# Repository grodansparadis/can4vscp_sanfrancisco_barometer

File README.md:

<h1>CAN4VSCP San Franscisco - barometer module</h1>

VSCP Barometer module.

<hr>

This project is part of the <a href="http://www.vscp.org">VSCP (Very Simple Control Protocol) project</a>. 

<hr>

This project is licensed under the 
<a href="http://creativecommons.org/licenses/by-nc-sa/3.0/">Creative Commons open source license Attribution-NonCommercial-ShareAlike 3.0 Unported</a>. 
Other license options are available by conacting <a href="malto:info@grodansparadis.com">Paradis of the Frog AB</a>

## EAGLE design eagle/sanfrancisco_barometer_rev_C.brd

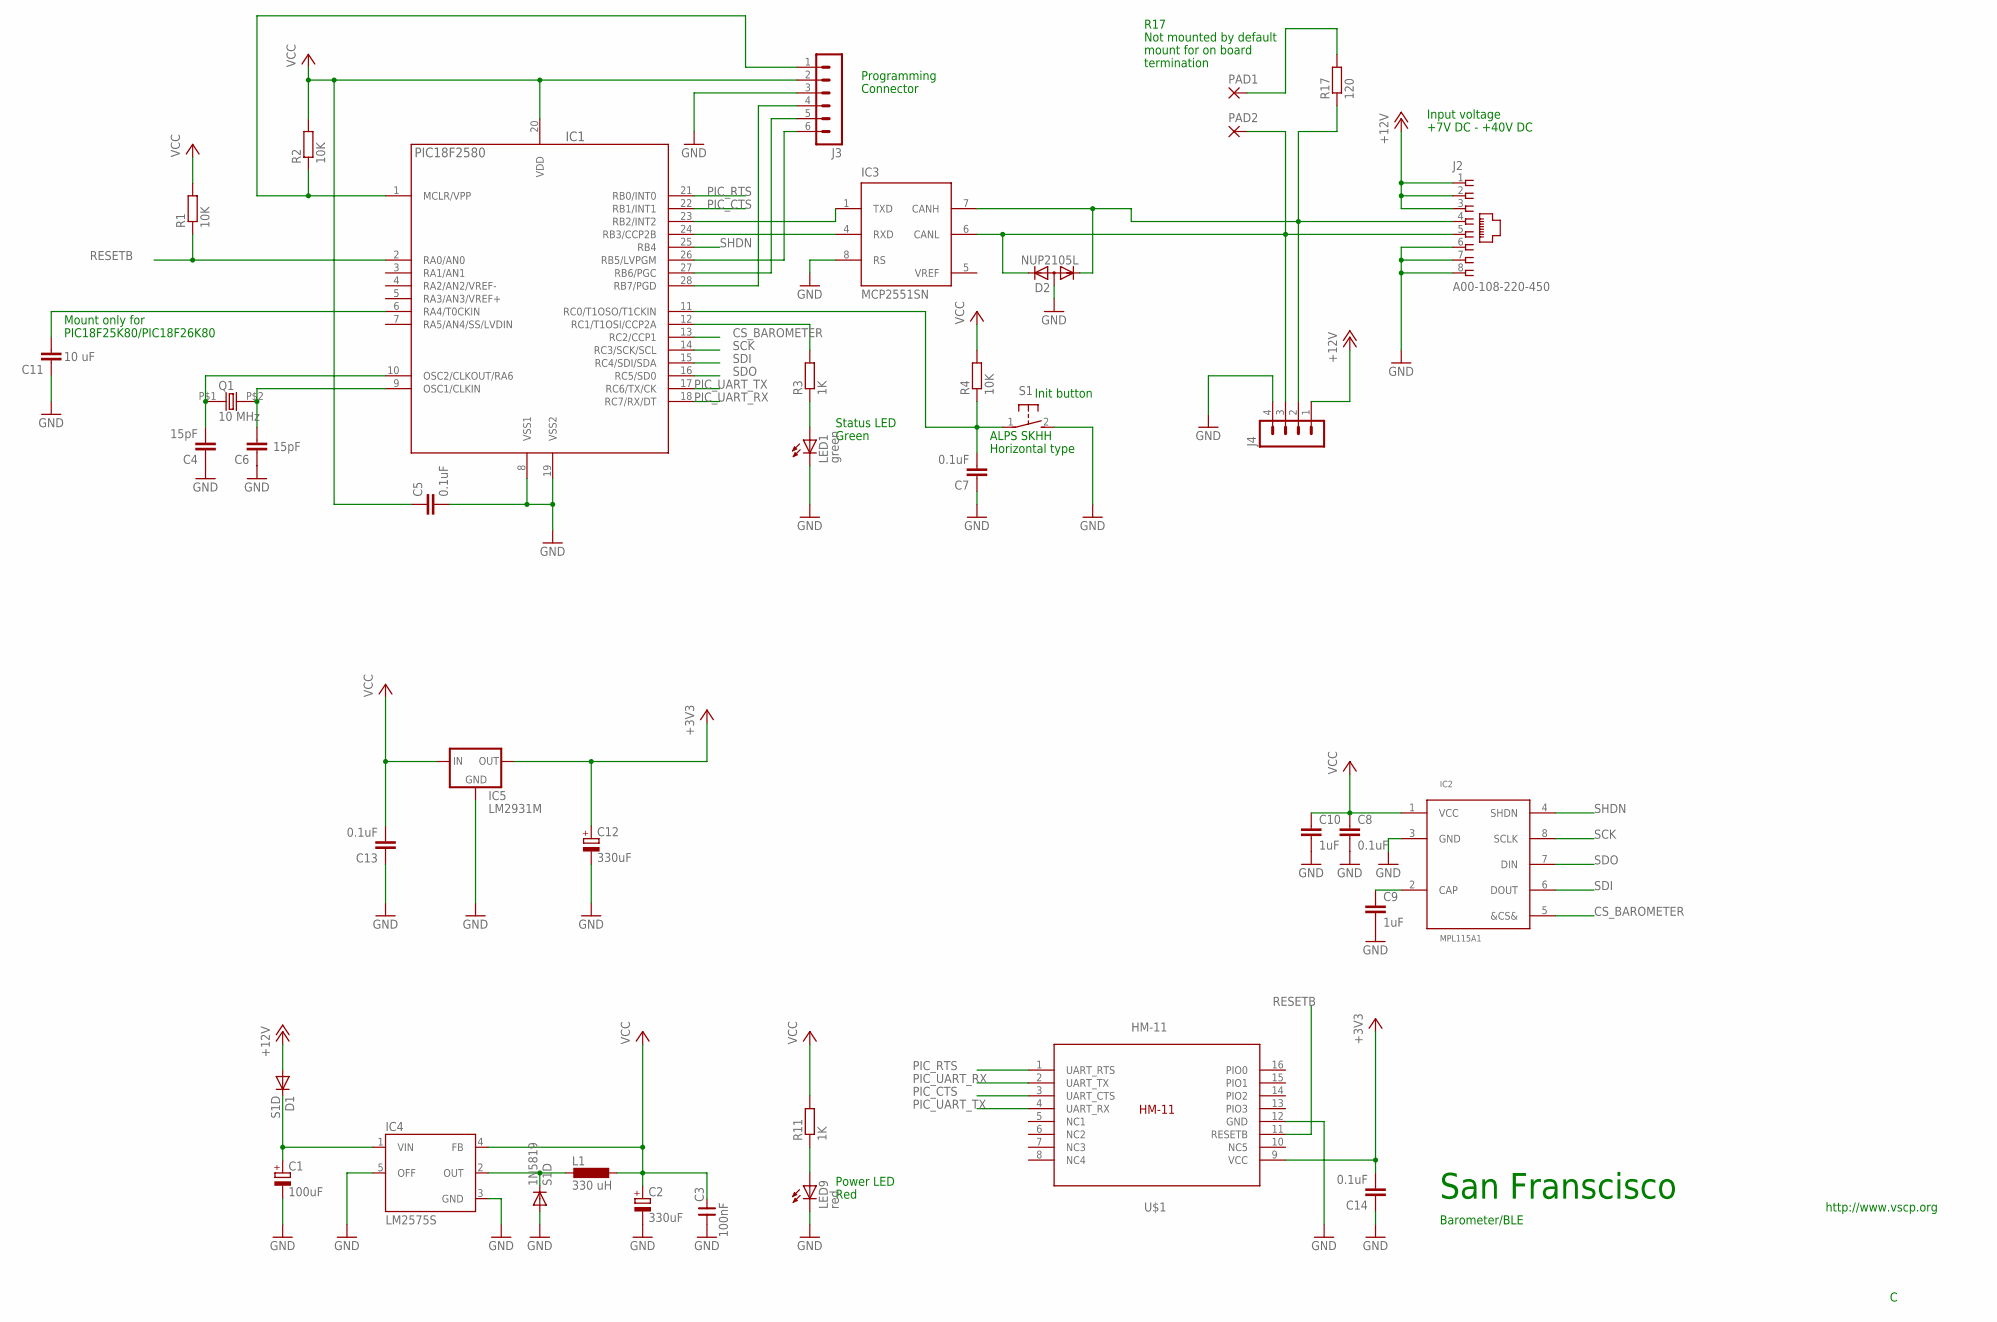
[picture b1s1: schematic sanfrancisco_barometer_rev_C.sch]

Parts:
1N5819: S1D; SOD123
C1: 100uF; PANASONIC_D
C2, C12: 330uF; PANASONIC_D
C3: 100nF; 0805
C4, C6: 15pF; C0805
C5, C7, C8, C13, C14: 0.1uF; C0805
C9, C10: 1uF; C0805
C11: 10 uF; C0805
D1: S1D; SOD123
D2: NUP2105L; SOT23
IC1: PIC18F2580; SO28
IC2: MPL115A1; LGA8
IC3: MCP2551SN; SO-08
IC4: LM2575S; TO263-5
IC5: LM2931M; SO08
J2: A00-108-220-450; RJ-45
J3: MA06-1
J4: MA04-1
L1: 330 uH; DO3316P
LED1: green; CHIP-LED0805
LED9: red; CHIP-LED0805
PAD1, PAD2: 1,6/0,8
Q1: 10 MHz; 9C
R1, R2, R4: 10K; R0805
R3, R11: 1K; R0805
R17: 120; R0805
S1: 31-XX; B3F-31XX
U$1: HM-11

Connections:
+3V3: C12.+, C14.2, IC5.1 (OUT), U$1.9 (VCC)
+12V: D1.A, J2.1, J2.2, J2.3, J4.1
CANL: D2.2 (K2), IC3.6 (CANL), J2.5, J4.3, PAD2.1
CS_BAROMETER: IC1.13 (RC2/CCP1), IC2.5 (&CS&)
GND: 1N5819.A, C1.-, C2.-, C3.1, C4.1, C5.2, C6.1, C7.1, C8.2, C9.2, C10.2, C11.1, C12.-, C13.1, C14.1, D2.3 (A), IC1.8 (VSS1), IC1.19 (VSS2), IC2.3 (GND), IC3.2 (VSS), IC3.8 (RS), IC4.3 (GND), IC4.5 (OFF), IC5.2 (GND), J2.6, J2.7, J2.8, J3.3, J4.4, LED1.C, LED9.C, S1.2 (S), U$1.12 (GND)
unnamed: 1N5819.C, IC4.2 (OUT), L1.1
unnamed: C4.2, IC1.10 (OSC2/CLKOUT/RA6), Q1.P$1 (1)
unnamed: C1.+, D1.C, IC4.1 (VIN)
unnamed: IC1.12 (RC1/T1OSI/CCP2A), R3.2
unnamed: LED1.A, R3.1
unnamed: C7.2, IC1.11 (RC0/T1OSO/T1CKIN), R4.1, S1.1
unnamed: C6.2, IC1.9 (OSC1/CLKIN), Q1.P$2 (2)
unnamed: C11.2, IC1.6 (RA4/T0CKIN)
unnamed: C9.1, IC2.2 (CAP)
unnamed: IC1.1 (MCLR/VPP), J3.1, R2.1
unnamed: IC1.28 (RB7/PGD), J3.4
unnamed: IC1.27 (RB6/PGC), J3.5
unnamed: IC1.26 (RB5/LVPGM), J3.6
unnamed: PAD1.1, R17.2
unnamed: LED9.A, R11.1
unnamed: D2.1 (K1), IC3.7 (CANH), J2.4, J4.2, R17.1
PIC_CTS: IC1.22 (RB1/INT1), U$1.3 (UART_CTS)
PIC_RTS: IC1.21 (RB0/INT0), U$1.1 (UART_RTS)
PIC_UART_RX: IC1.18 (RC7/RX/DT), U$1.2 (UART_TX)
PIC_UART_TX: IC1.17 (RC6/TX/CK), U$1.4 (UART_RX)
RESETB: IC1.2 (RA0/AN0), R1.1, U$1.11 (RESETB)
RXCAN: IC1.24 (RB3/CCP2B), IC3.4 (RXD)
SCK: IC1.14 (RC3/SCK/SCL), IC2.8 (SCLK)
SDI: IC1.15 (RC4/SDI/SDA), IC2.6 (DOUT)
SDO: IC1.16 (RC5/SD0), IC2.7 (DIN)
SHDN: IC1.25 (RB4), IC2.4 (SHDN)
TXCAN: IC1.23 (RB2/INT2), IC3.1 (TXD)
VCC: C2.+, C3.2, C5.1, C8.1, C10.1, C13.2, IC1.20 (VDD), IC2.1 (VCC), IC3.3 (VDD), IC4.4 (FB), IC5.8 (IN), J3.2, L1.2, R1.2, R2.2, R4.2, R11.2
VREF: IC3.5 (VREF)

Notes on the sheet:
Init button
Status LED
Programming
Connector
ALPS SKHH
Horizontal type
San Franscisco
http://www.vscp.org
Input voltage
+7V DC - +40V DC
Power LED
Red
Green
Mount only for
PIC18F25K80/PIC18F26K80
Not mounted by default
mount for on board
termination
R17
Barometer/BLE

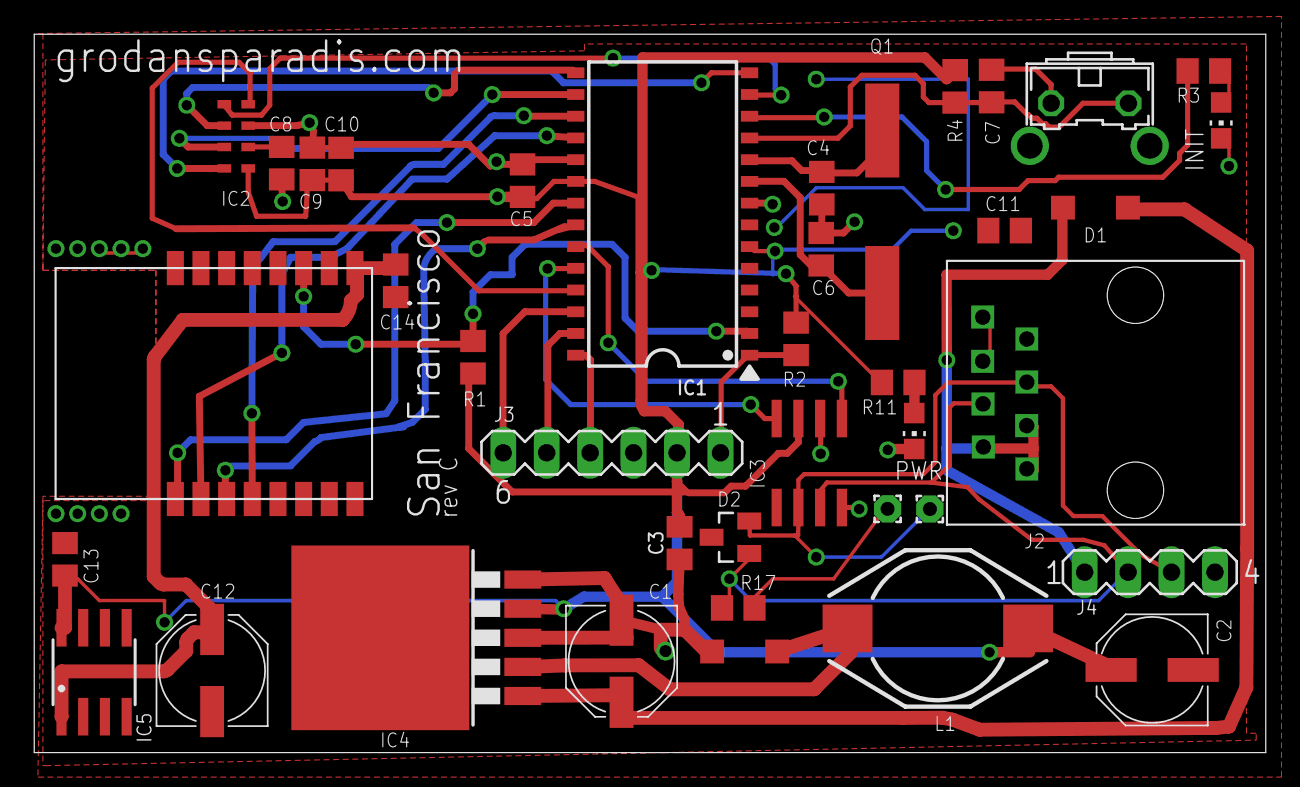
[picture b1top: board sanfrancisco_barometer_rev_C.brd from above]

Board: 2 copper layers, 72.0 x 42.0 mm, 39 parts (0 on the bottom side), 33 nets.

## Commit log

2015-08-17 Changed license to Artistic License 3.0
2015-08-23 Added schema for San Franscisco
2015-12-17 Updated license
2016-10-14 Changed component symbols
2018-11-07 Initial mdf sketch
